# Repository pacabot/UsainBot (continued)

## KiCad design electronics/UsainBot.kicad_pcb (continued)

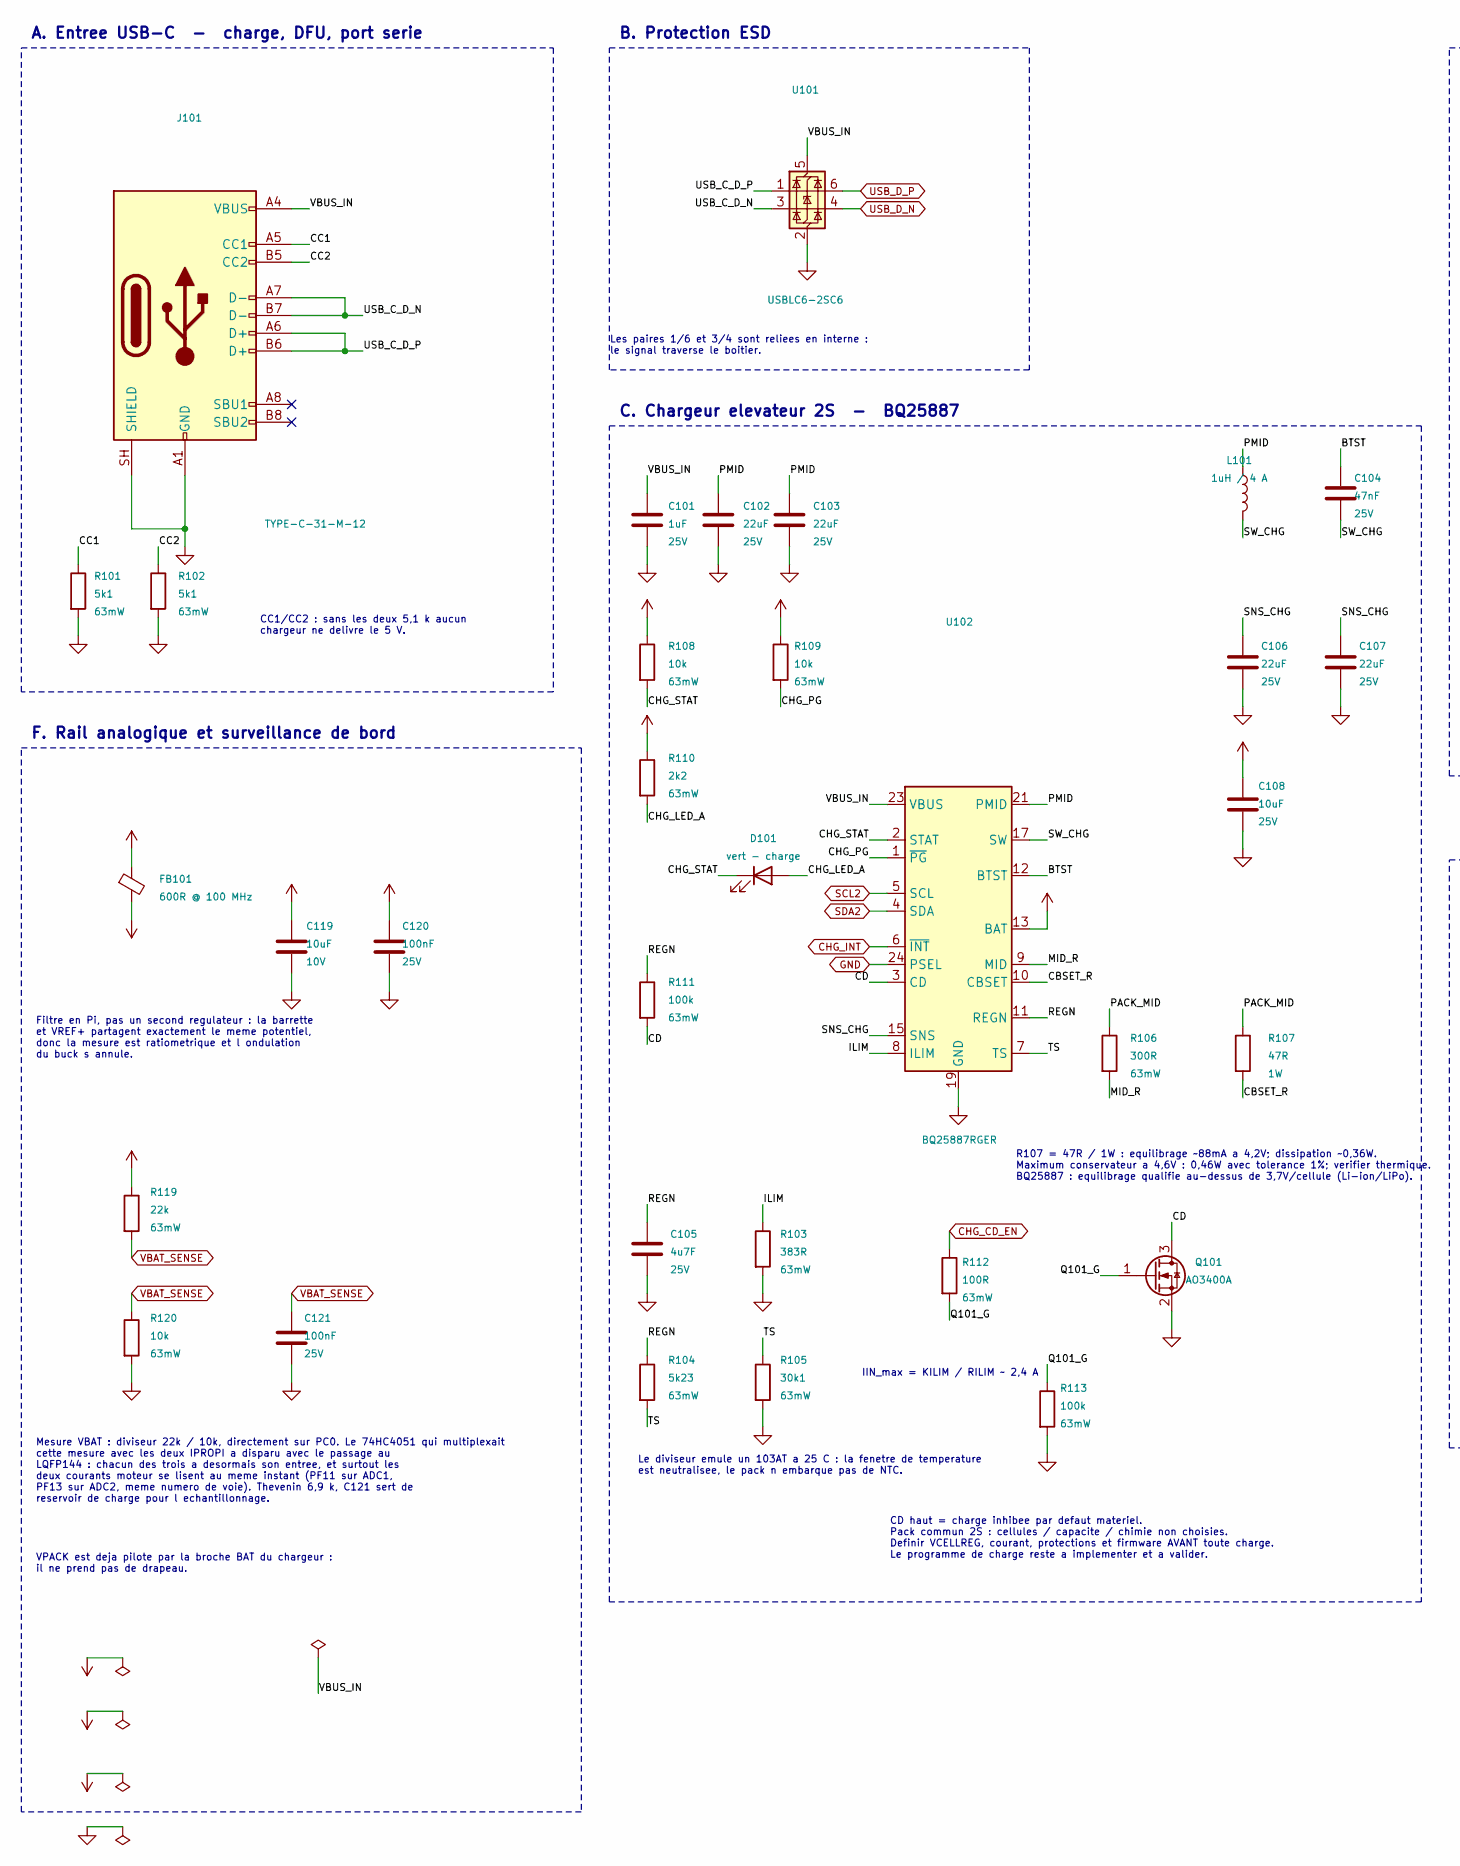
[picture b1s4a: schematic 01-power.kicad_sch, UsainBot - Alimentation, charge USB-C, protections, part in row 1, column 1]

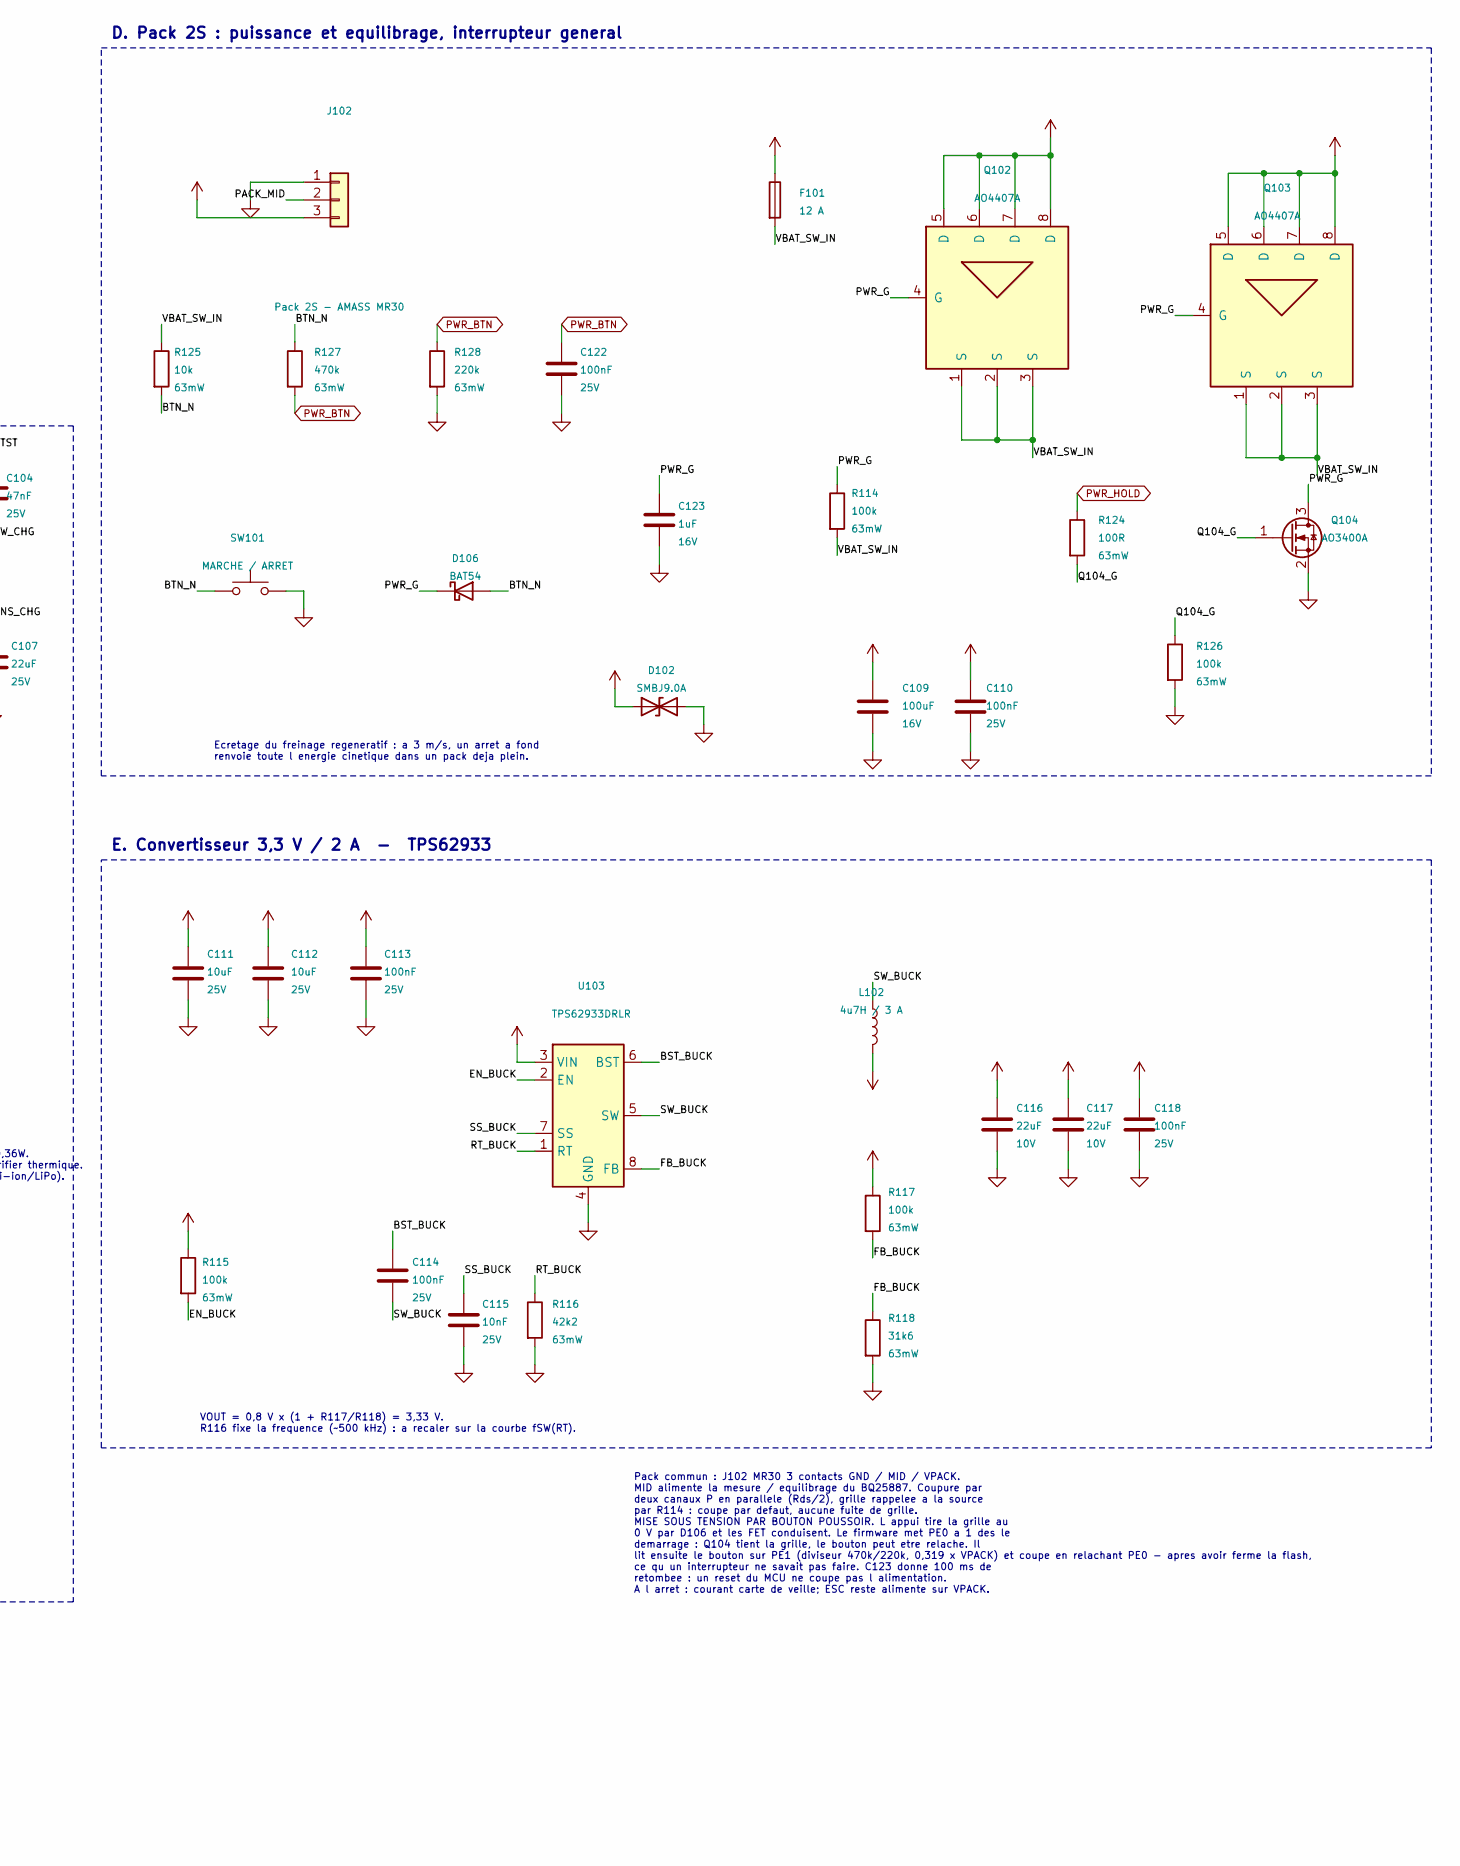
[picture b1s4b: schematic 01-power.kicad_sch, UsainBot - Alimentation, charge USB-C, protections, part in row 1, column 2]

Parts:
C101: 1uF; C_0603_1608Metric; Voltage 25V
C102, C103, C106, C107: 22uF; C_1210_3225Metric; Voltage 25V
C104: 47nF; C_0402_1005Metric; Voltage 25V
C105: 4u7F; C_0805_2012Metric; Voltage 25V
C108: 10uF; C_0805_2012Metric; Voltage 25V
C109: 100uF; CP_Elec_6.3x7.7; Voltage 16V
C110, C113, C114, C118, C120, C121, C122: 100nF; C_0402_1005Metric; Voltage 25V
C111, C112: 10uF; C_1210_3225Metric; Voltage 25V
C115: 10nF; C_0402_1005Metric; Voltage 25V
C116, C117: 22uF; C_0805_2012Metric; Voltage 10V
C119: 10uF; C_0805_2012Metric; Voltage 10V
C123: 1uF; C_0402_1005Metric; Voltage 16V
D101: vert - charge; LED_0603_1608Metric
D102: SMBJ9.0A; D_SMB
D106: BAT54; D_SOD-323
F101: 12 A; R_1206_3216Metric
FB101: 600R @ 100 MHz; L_0805_2012Metric
J101: TYPE-C-31-M-12; USB_C_Receptacle_HRO_TYPE-C-31-M-12; LCSC C165948
J102: Pack 2S - AMASS MR30; AMASS_MR30PB-M_1x03_P3.50mm_Vertical; MPN MR30PB-M30.G.Y
L101: 1uH / 4 A; L_Taiyo-Yuden_NR-30xx
L102: 4u7H / 3 A; L_Taiyo-Yuden_NR-40xx
Q101, Q104: AO3400A; SOT-23
Q102, Q103: AO4407A; SOIC-8_3.9x4.9mm_P1.27mm
R101, R102: 5k1; R_0402_1005Metric
R103: 383R; R_0402_1005Metric
R104: 5k23; R_0402_1005Metric
R105: 30k1; R_0402_1005Metric
R106: 300R; R_0402_1005Metric
R107: 47R; R_2512_6332Metric
R108, R109, R120, R125: 10k; R_0402_1005Metric
R110: 2k2; R_0402_1005Metric
R111, R113, R114, R115, R117, R126: 100k; R_0402_1005Metric
R112, R124: 100R; R_0402_1005Metric
R116: 42k2; R_0402_1005Metric
R118: 31k6; R_0402_1005Metric
R119: 22k; R_0402_1005Metric
R127: 470k; R_0402_1005Metric
R128: 220k; R_0402_1005Metric
SW101: MARCHE / ARRET; SW_SPST_B3U-1000P
U101: USBLC6-2SC6; SOT-23-6
U102: BQ25887RGER; HVQFN-24-1EP_4x4mm_P0.5mm_EP2.6x2.6mm_ThermalVias; LCSC C2761614
U103: TPS62933DRLR; SOT-583-8; LCSC C3200405

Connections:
/Alimentation/BST_BUCK: C114.1, U103.6 (BST)
/Alimentation/BTN_N: D106.2 (A), R125.2, R127.1, SW101.1
/Alimentation/BTST: C104.1, U102.12 (BTST)
/Alimentation/CBSET_R: R107.2, U102.10 (CBSET)
/Alimentation/CC1: J101.A5 (CC1), R101.1
/Alimentation/CC2: J101.B5 (CC2), R102.1
/Alimentation/CD: Q101.3 (D), R111.2, U102.3 (CD)
/Alimentation/CHG_LED_A: D101.2 (A), R110.2
/Alimentation/CHG_PG: R109.2, U102.1 (~PG)
/Alimentation/CHG_STAT: D101.1 (K), R108.2, U102.2 (STAT)
/Alimentation/EN_BUCK: R115.2, U103.2 (EN)
/Alimentation/FB_BUCK: R117.2, R118.1, U103.8 (FB)
/Alimentation/ILIM: R103.1, U102.8 (ILIM)
/Alimentation/MID_R: R106.2, U102.9 (MID)
/Alimentation/PACK_MID: J102.2, R106.1, R107.1
/Alimentation/PMID: C102.1, C103.1, L101.1, U102.21 (PMID), U102.22 (PMID)
/Alimentation/PWR_G: C123.1, D106.1 (K), Q102.4 (G), Q103.4 (G), Q104.3 (D), R114.1
/Alimentation/Q101_G: Q101.1 (G), R112.2, R113.1
/Alimentation/Q104_G: Q104.1 (G), R124.2, R126.1
/Alimentation/REGN: C105.1, R104.1, R111.1, U102.11 (REGN)
/Alimentation/RT_BUCK: R116.1, U103.1 (RT)
/Alimentation/SNS_CHG: C106.1, C107.1, U102.15 (SNS), U102.16 (SNS)
/Alimentation/SS_BUCK: C115.1, U103.7 (SS)
/Alimentation/SW_BUCK: C114.2, L102.1, U103.5 (SW)
/Alimentation/SW_CHG: C104.2, L101.2, U102.17 (SW), U102.18 (SW)
/Alimentation/TS: R104.2, R105.1, U102.7 (TS)
/Alimentation/USB_C_D_N: J101.A7 (D-), J101.B7 (D-), U101.3 (I/O2)
/Alimentation/USB_C_D_P: J101.A6 (D+), J101.B6 (D+), U101.1 (I/O1)
/Alimentation/VBAT_SW_IN: F101.2, Q102.1 (S), Q102.2 (S), Q102.3 (S), Q103.1 (S), Q103.2 (S), Q103.3 (S), R114.2, R125.1
CHG_CD_EN: R112.1; also elsewhere on the board
CHG_INT: U102.6 (~INT); also elsewhere on the board
PWR_BTN: C122.1, R127.2, R128.1; also elsewhere on the board
PWR_HOLD: R124.1; also elsewhere on the board
SCL2: U102.5 (SCL); also elsewhere on the board
SDA2: U102.4 (SDA); also elsewhere on the board
USB_D_N: U101.4 (I/O2); also elsewhere on the board
USB_D_P: U101.6 (I/O1); also elsewhere on the board
VBAT_SENSE: C121.1, R119.2, R120.1; also elsewhere on the board
VPACK: C108.1, F101.1, J102.3, U102.13 (BAT), U102.14 (BAT); also elsewhere on the board

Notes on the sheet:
Le diviseur emule un 103AT a 25 C : la fenetre de temperature est neutralisee, le pack n embarque pas de NTC.
B. Protection ESD
A. Entree USB-C - charge, DFU, port serie
E. Convertisseur 3,3 V / 2 A - TPS62933
F. Rail analogique et surveillance de bord
CD haut = charge inhibee par defaut materiel. Pack commun 2S : cellules / capacite / chimie non choisies. Definir VCELLREG, courant, protections et firmware AVANT toute charge. Le programme de charge reste a implementer et a valider.
VPACK est deja pilote par la broche BAT du chargeur : il ne prend pas de drapeau.
CC1/CC2 : sans les deux 5,1 k aucun chargeur ne delivre le 5 V.
Les paires 1/6 et 3/4 sont reliees en interne : le signal traverse le boitier.
Ecretage du freinage regeneratif : a 3 m/s, un arret a fond renvoie toute l energie cinetique dans un pack deja plein.
D. Pack 2S : puissance et equilibrage, interrupteur general
C. Chargeur elevateur 2S - BQ25887
Pack commun : J102 MR30 3 contacts GND / MID / VPACK. MID alimente la mesure / equilibrage du BQ25887. Coupure par deux canaux P en parallele (Rds/2), grille rappelee a la source par R114 : coupe par defaut, aucune fuite de grille. MISE SOUS TENSION PAR BOUTON POUSSOIR. L appui tire la grille au 0 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
R107 = 47R / 1W : equilibrage ~88mA a 4,2V; dissipation ~0,36W. Maximum conservateur a 4,6V : 0,46W avec tolerance 1%; verifier thermique. BQ25887 : equilibrage qualifie au-dessus de 3,7V/cellule (Li-ion/LiPo).
Mesure VBAT : diviseur 22k / 10k, directement sur PC0. Le 74HC4051 qui multiplexait cette mesure avec les deux IPROPI a disparu avec le passage au LQFP144 : chacun des trois a desormais son entree, et surtout les deux courants moteur se lisent au meme instant (PF11 sur ADC1, PF13 sur ADC2, meme num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
Filtre en Pi, pas un second regulateur : la barrette et VREF+ partagent exactement le meme potentiel, donc la mesure est ratiometrique et l ondulation du buck s annule.
IIN_max = KILIM / RILIM ~ 2,4 A
VOUT = 0,8 V x (1 + R117/R118) = 3,33 V. R116 fixe la frequence (~500 kHz) : a recaler sur la courbe fSW(RT).

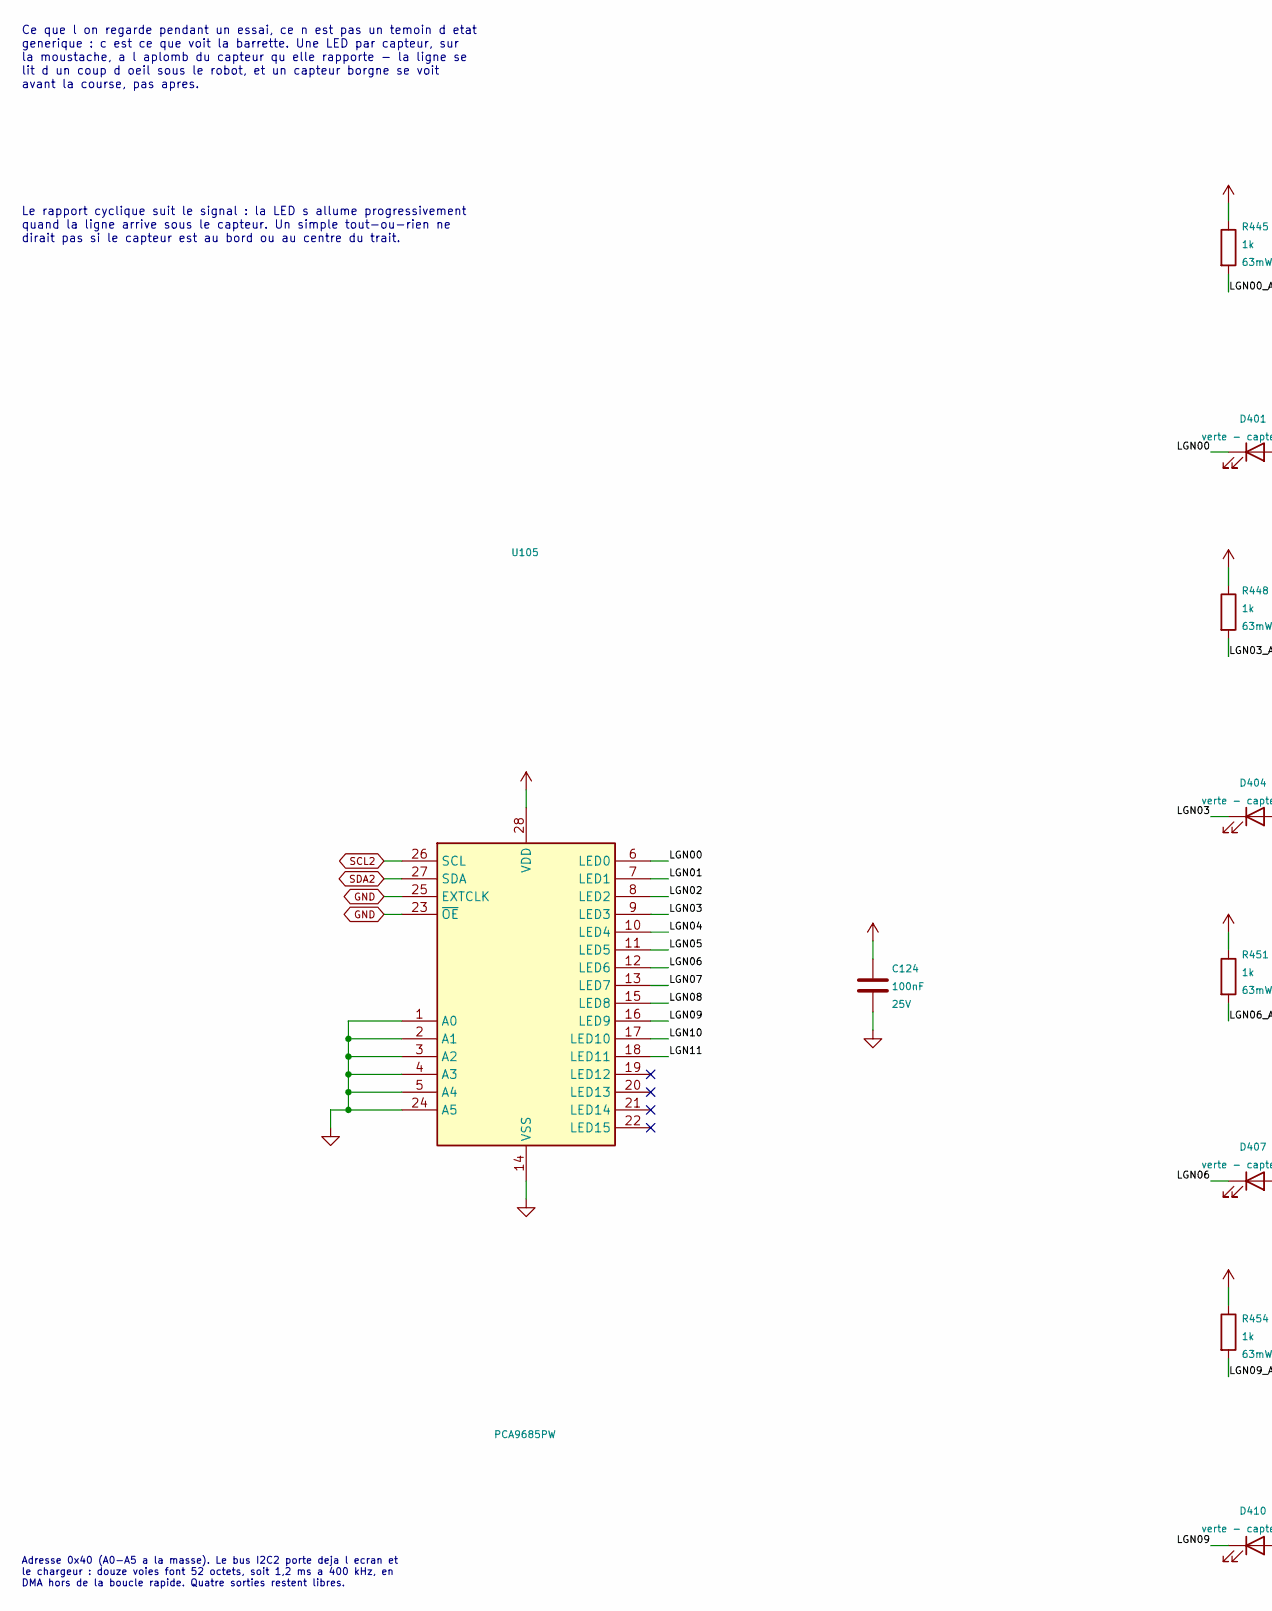
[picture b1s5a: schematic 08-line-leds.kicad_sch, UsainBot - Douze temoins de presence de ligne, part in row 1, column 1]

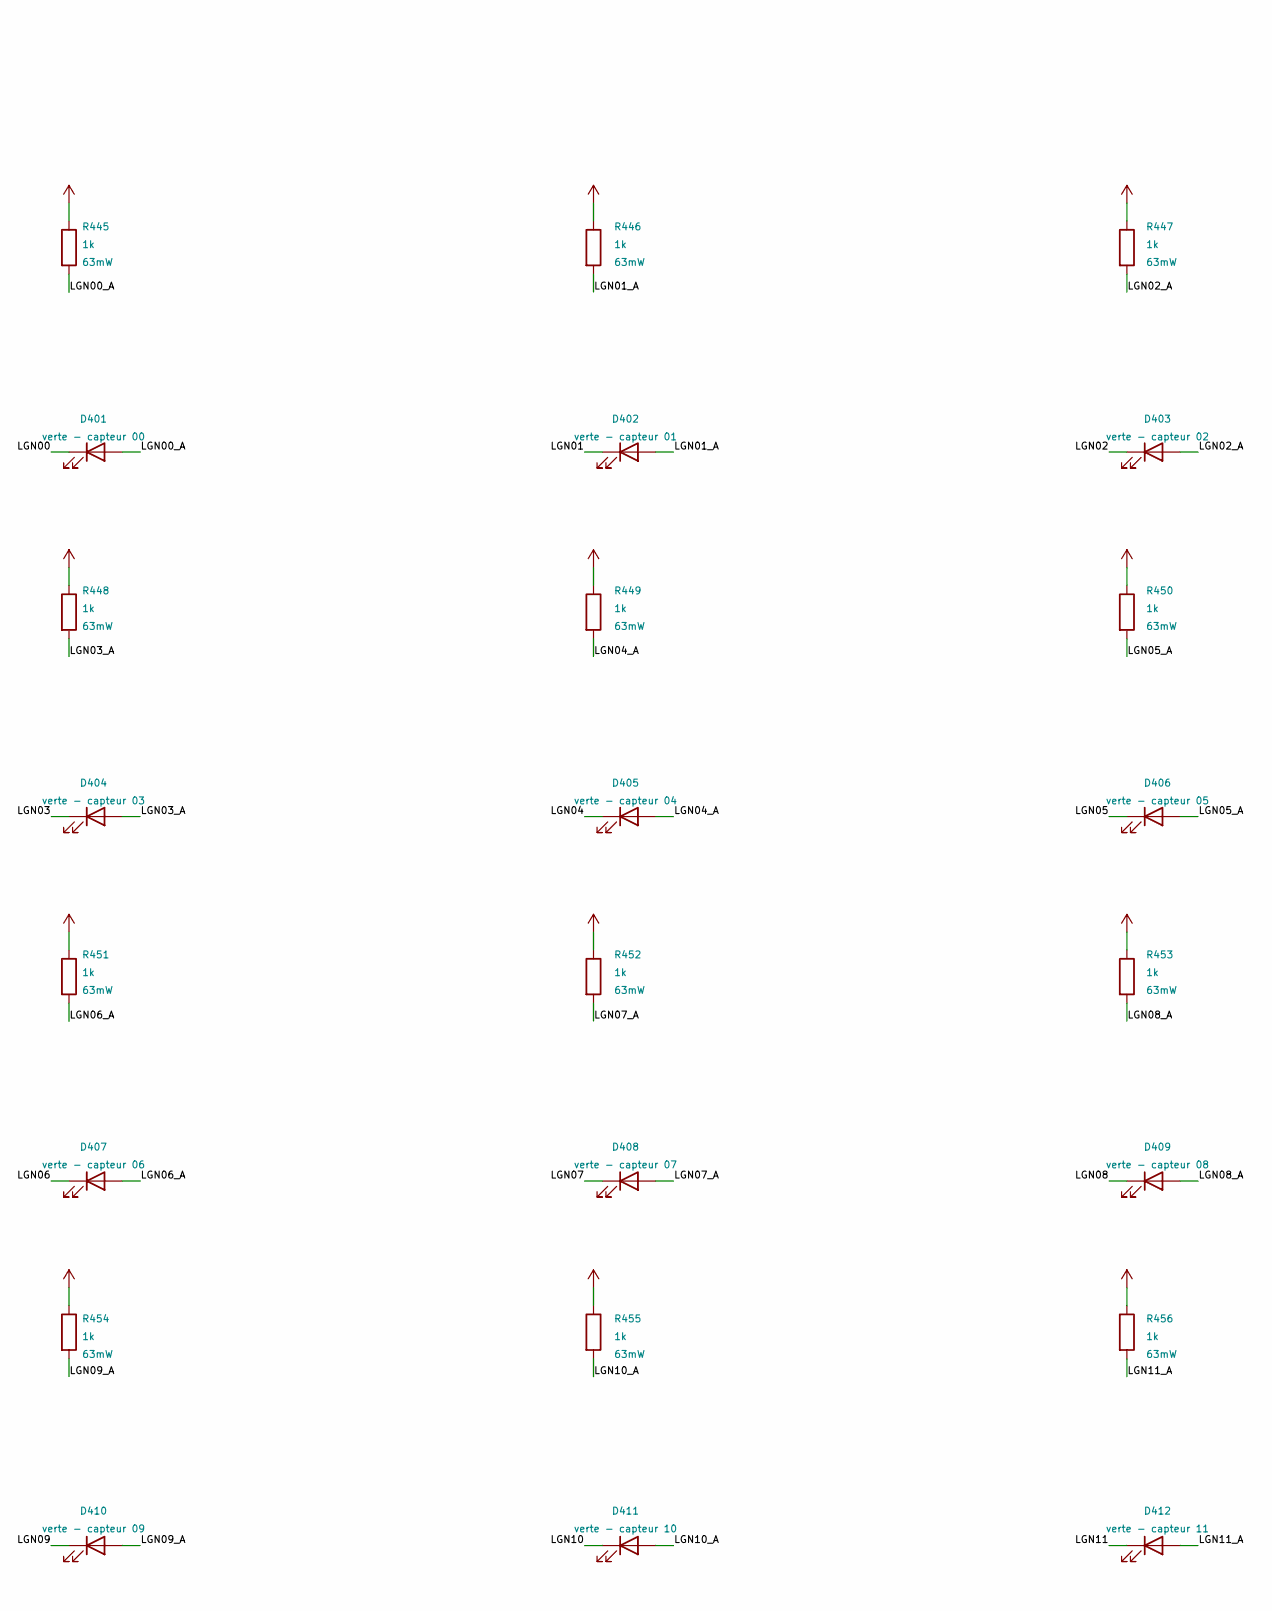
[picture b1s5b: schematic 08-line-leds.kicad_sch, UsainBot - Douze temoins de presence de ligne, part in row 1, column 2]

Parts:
C124: 100nF; C_0402_1005Metric; Voltage 25V
D401: verte - capteur 00; LED_0603_1608Metric
D402: verte - capteur 01; LED_0603_1608Metric
D403: verte - capteur 02; LED_0603_1608Metric
D404: verte - capteur 03; LED_0603_1608Metric
D405: verte - capteur 04; LED_0603_1608Metric
D406: verte - capteur 05; LED_0603_1608Metric
D407: verte - capteur 06; LED_0603_1608Metric
D408: verte - capteur 07; LED_0603_1608Metric
D409: verte - capteur 08; LED_0603_1608Metric
D410: verte - capteur 09; LED_0603_1608Metric
D411: verte - capteur 10; LED_0603_1608Metric
D412: verte - capteur 11; LED_0603_1608Metric
R445, R446, R447, R448, R449, R450, R451, R452, R453, R454, R455, R456: 1k; R_0402_1005Metric
U105: PCA9685PW; TSSOP-28_4.4x9.7mm_P0.65mm

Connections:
/Temoins de ligne/LGN00: D401.1 (K), U105.6 (LED0)
/Temoins de ligne/LGN00_A: D401.2 (A), R445.2
/Temoins de ligne/LGN01: D402.1 (K), U105.7 (LED1)
/Temoins de ligne/LGN01_A: D402.2 (A), R446.2
/Temoins de ligne/LGN02: D403.1 (K), U105.8 (LED2)
/Temoins de ligne/LGN02_A: D403.2 (A), R447.2
/Temoins de ligne/LGN03: D404.1 (K), U105.9 (LED3)
/Temoins de ligne/LGN03_A: D404.2 (A), R448.2
/Temoins de ligne/LGN04: D405.1 (K), U105.10 (LED4)
/Temoins de ligne/LGN04_A: D405.2 (A), R449.2
/Temoins de ligne/LGN05: D406.1 (K), U105.11 (LED5)
/Temoins de ligne/LGN05_A: D406.2 (A), R450.2
/Temoins de ligne/LGN06: D407.1 (K), U105.12 (LED6)
/Temoins de ligne/LGN06_A: D407.2 (A), R451.2
/Temoins de ligne/LGN07: D408.1 (K), U105.13 (LED7)
/Temoins de ligne/LGN07_A: D408.2 (A), R452.2
/Temoins de ligne/LGN08: D409.1 (K), U105.15 (LED8)
/Temoins de ligne/LGN08_A: D409.2 (A), R453.2
/Temoins de ligne/LGN09: D410.1 (K), U105.16 (LED9)
/Temoins de ligne/LGN09_A: D410.2 (A), R454.2
/Temoins de ligne/LGN10: D411.1 (K), U105.17 (LED10)
/Temoins de ligne/LGN10_A: D411.2 (A), R455.2
/Temoins de ligne/LGN11: D412.1 (K), U105.18 (LED11)
/Temoins de ligne/LGN11_A: D412.2 (A), R456.2
SCL2: U105.26 (SCL); also elsewhere on the board
SDA2: U105.27 (SDA); also elsewhere on the board

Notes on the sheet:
Ce que l on regarde pendant un essai, ce n est pas un temoin d etat generique : c est ce que voit la barrette. Une LED par capteur, sur la moustache, a l aplomb du capteur qu elle rapporte - la ligne se lit d un coup d oeil sous le robot, et un capteur borgne se voit avant la course, pas apres.
Le rapport cyclique suit le signal : la LED s allume progressivement quand la ligne arrive sous le capteur. Un simple tout-ou-rien ne dirait pas si le capteur est au bord ou au centre du trait.
Adresse 0x40 (A0-A5 a la masse). Le bus I2C2 porte deja l ecran et le chargeur : douze voies font 52 octets, soit 1,2 ms a 400 kHz, en DMA hors de la boucle rapide. Quatre sorties restent libres.

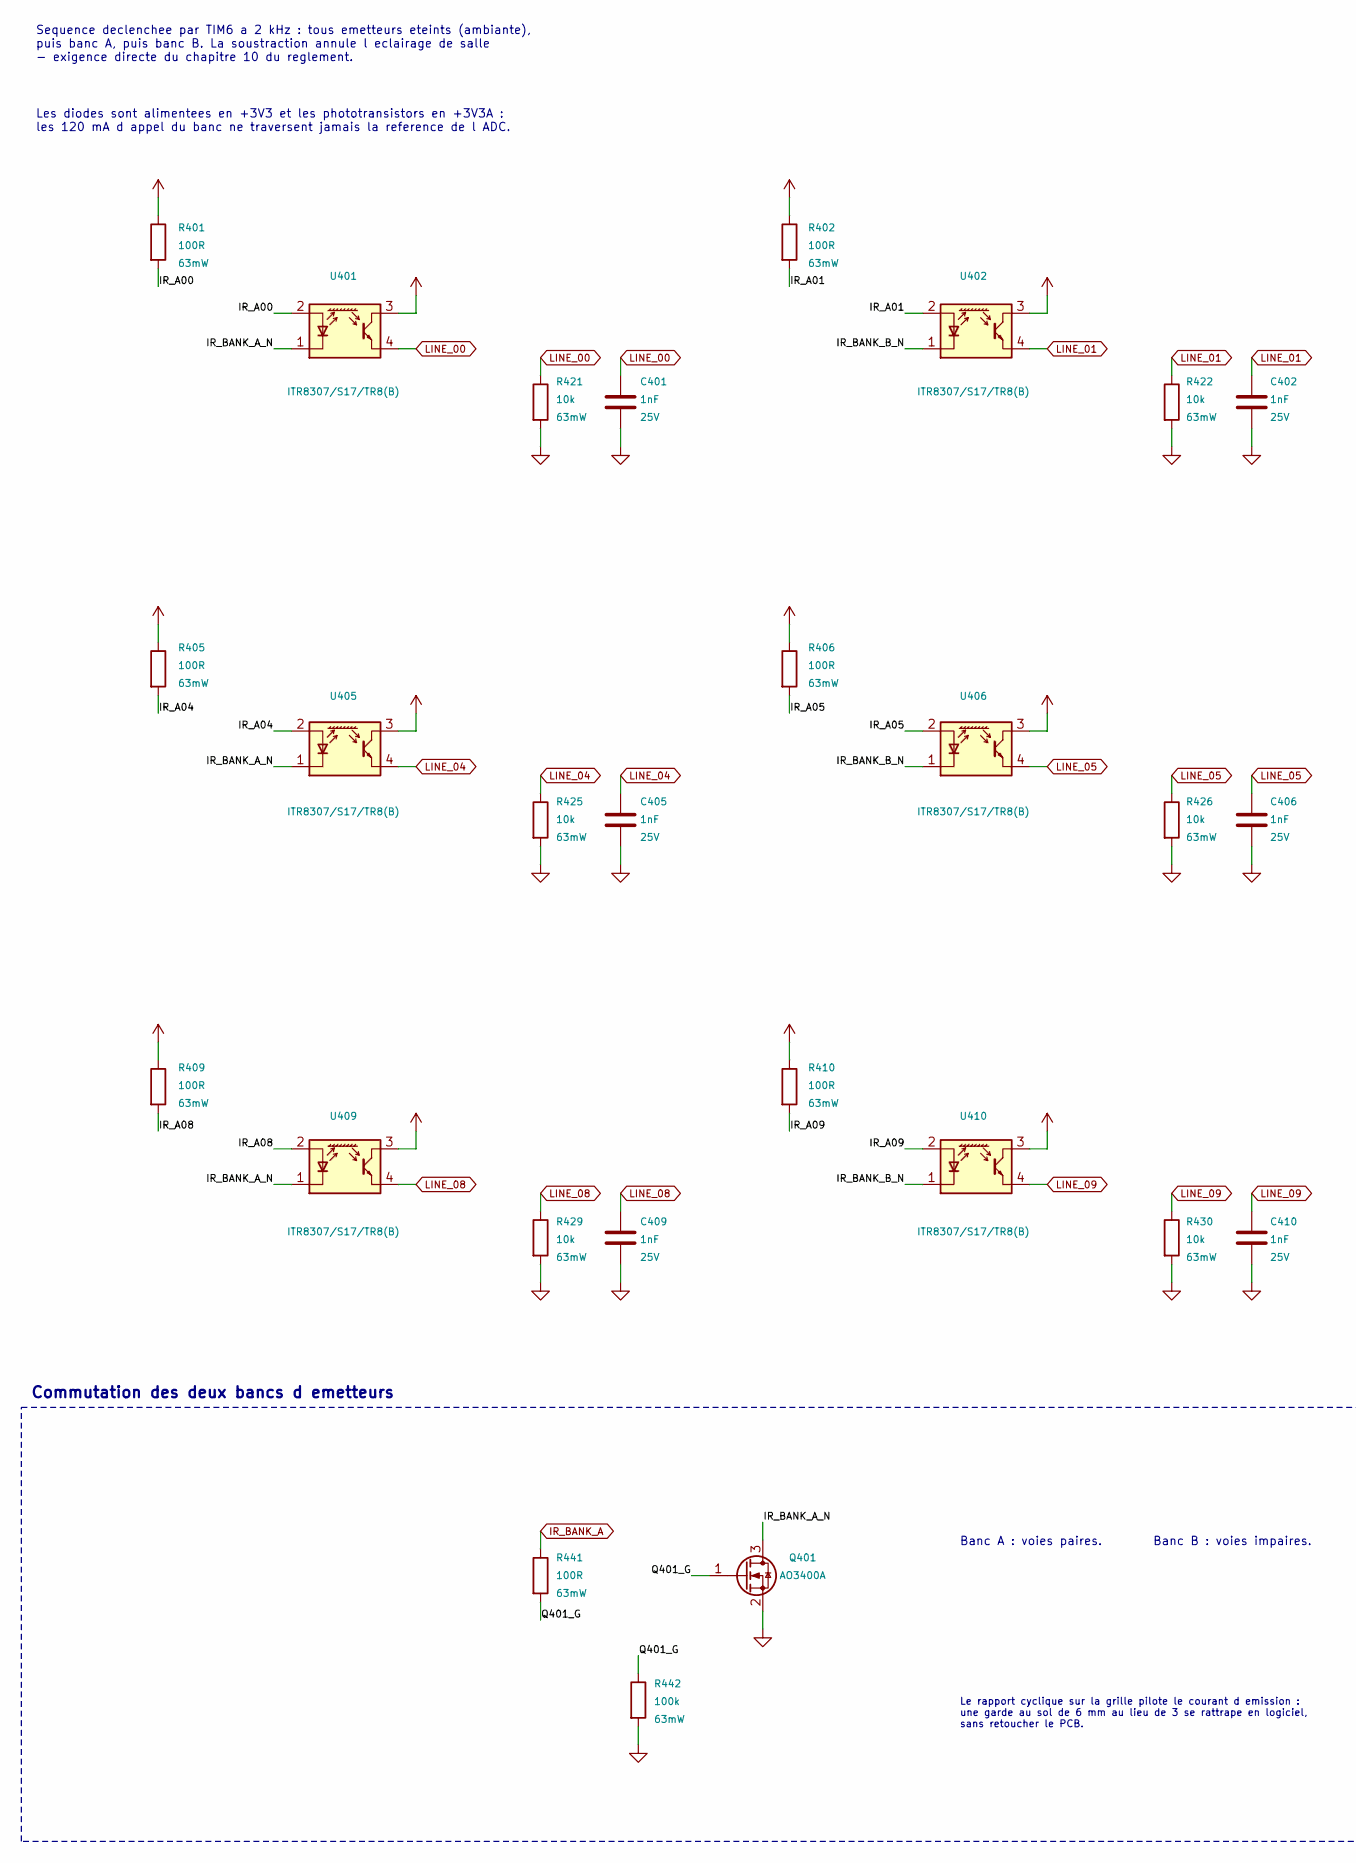
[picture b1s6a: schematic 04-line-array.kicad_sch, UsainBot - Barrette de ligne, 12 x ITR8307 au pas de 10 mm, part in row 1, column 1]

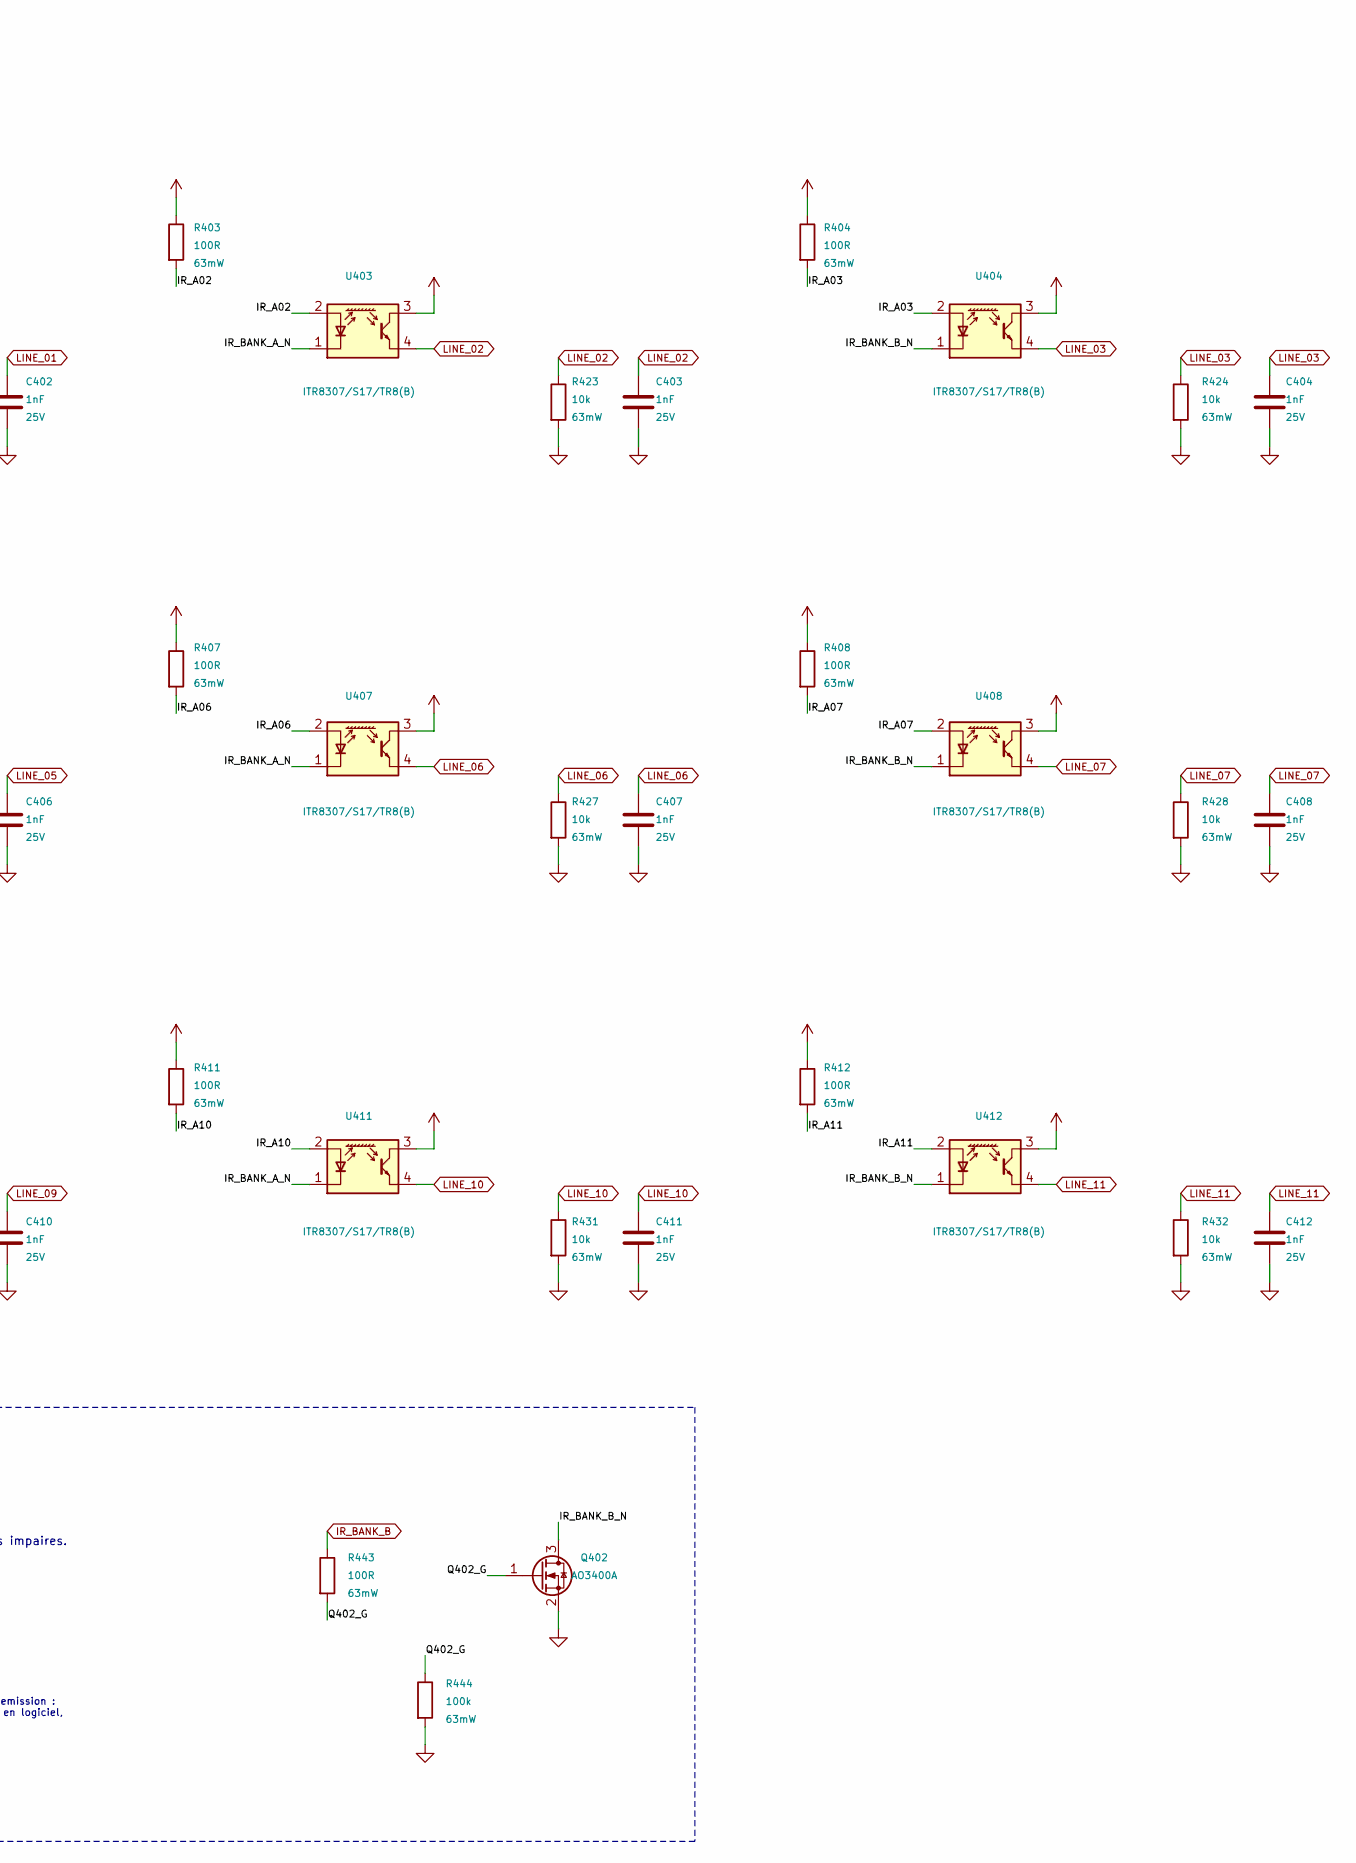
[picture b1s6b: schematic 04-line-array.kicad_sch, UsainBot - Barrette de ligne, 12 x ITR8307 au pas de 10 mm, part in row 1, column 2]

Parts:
C401, C402, C403, C404, C405, C406, C407, C408, C409, C410, C411, C412: 1nF; C_0402_1005Metric; Voltage 25V
Q401, Q402: AO3400A; SOT-23
R401, R402, R403, R404, R405, R406, R407, R408, R409, R410, R411, R412, R441, R443: 100R; R_0402_1005Metric
R421, R422, R423, R424, R425, R426, R427, R428, R429, R430, R431, R432: 10k; R_0402_1005Metric
R442, R444: 100k; R_0402_1005Metric
U401, U402, U403, U404, U405, U406, U407, U408, U409, U410, U411, U412: ITR8307/S17/TR8(B); ITR8307_S17_TR8_Bottom; LCSC C81632

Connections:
/Barrette/IR_A00: R401.2, U401.2 (A)
/Barrette/IR_A01: R402.2, U402.2 (A)
/Barrette/IR_A02: R403.2, U403.2 (A)
/Barrette/IR_A03: R404.2, U404.2 (A)
/Barrette/IR_A04: R405.2, U405.2 (A)
/Barrette/IR_A05: R406.2, U406.2 (A)
/Barrette/IR_A06: R407.2, U407.2 (A)
/Barrette/IR_A07: R408.2, U408.2 (A)
/Barrette/IR_A08: R409.2, U409.2 (A)
/Barrette/IR_A09: R410.2, U410.2 (A)
/Barrette/IR_A10: R411.2, U411.2 (A)
/Barrette/IR_A11: R412.2, U412.2 (A)
/Barrette/IR_BANK_A_N: Q401.3 (D), U401.1 (K), U403.1 (K), U405.1 (K), U407.1 (K), U409.1 (K), U411.1 (K)
/Barrette/IR_BANK_B_N: Q402.3 (D), U402.1 (K), U404.1 (K), U406.1 (K), U408.1 (K), U410.1 (K), U412.1 (K)
/Barrette/Q401_G: Q401.1 (G), R441.2, R442.1
/Barrette/Q402_G: Q402.1 (G), R443.2, R444.1
IR_BANK_A: R441.1; also elsewhere on the board
IR_BANK_B: R443.1; also elsewhere on the board
LINE_00: C401.1, R421.1, U401.4; also elsewhere on the board
LINE_01: C402.1, R422.1, U402.4; also elsewhere on the board
LINE_02: C403.1, R423.1, U403.4; also elsewhere on the board
LINE_03: C404.1, R424.1, U404.4; also elsewhere on the board
LINE_04: C405.1, R425.1, U405.4; also elsewhere on the board
LINE_05: C406.1, R426.1, U406.4; also elsewhere on the board
LINE_06: C407.1, R427.1, U407.4; also elsewhere on the board
LINE_07: C408.1, R428.1, U408.4; also elsewhere on the board
LINE_08: C409.1, R429.1, U409.4; also elsewhere on the board
LINE_09: C410.1, R430.1, U410.4; also elsewhere on the board
LINE_10: C411.1, R431.1, U411.4; also elsewhere on the board
LINE_11: C412.1, R432.1, U412.4; also elsewhere on the board

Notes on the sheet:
Banc A : voies paires. Banc B : voies impaires.
Les diodes sont alimentees en +3V3 et les phototransistors en +3V3A : les 120 mA d appel du banc ne traversent jamais la reference de l ADC.
Le rapport cyclique sur la grille pilote le courant d emission : une garde au sol de 6 mm au lieu de 3 se rattrape en logiciel, sans retoucher le PCB.
Sequence declenchee par TIM6 a 2 kHz : tous emetteurs eteints (ambiante), puis banc A, puis banc B. La soustraction annule l eclairage de salle - exigence directe du chapitre 10 du reglement.
Commutation des deux bancs d emetteurs
